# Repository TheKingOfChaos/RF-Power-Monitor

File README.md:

# RF-Power-Monitor

A mains power monitor built on a Raspberry Pi Pico with a W5500 Ethernet module. It reports whether mains power is present over SNMP v1 and v2c, including traps, together with standard interface statistics (IF-MIB), the CPU temperature and the ambient temperature (TMP1075 on the carrier board), so it can be monitored by LibreNMS or any other SNMP manager. It is configured through a menu on the USB serial port or a web page.

Current version: **3.6.1** (see [CHANGELOG.md](CHANGELOG.md)).

## Overview

An isolated detector (optocoupler with filtering) turns mains presence into a clean 3.3 V level on GPIO27; in the test setup an IKEA smart plug in front of it lets the tests switch mains off and on. The Pico's core 1 samples GPIO27 and the reset button (GPIO22) every millisecond; core 0 runs the network, the SNMP agent, the web page and the serial menu. Settings live in the Pico's flash in two copies, and the W5500 provides 10/100 Ethernet over SPI. On the network the device gets its address by DHCP (or a static IP), is reachable as `RF-Power-XXXXXX.local` (mDNS; XXXXXX = the last 6 hex digits of its MAC), answers SNMP v1/v2c on UDP 161, sends traps on UDP 162, serves a configuration web page with login on TCP 80, sets its clock by NTP and sends its events to a syslog server, when the network has them. The USB serial port carries the configuration menu and the hardware-in-the-loop tests. More diagrams are in [docs/diagrams/](docs/diagrams/README.md).

## Status

| Feature | State |
|---|---|
| Ethernet with DHCP (default) or static IP | Working |
| Serial menu for all settings | Working |
| Settings stored in flash, power-cut safe | Working |
| Factory reset button (GPIO22, 10 s hold, LED feedback) | Working, tested with the real button |
| Mains power monitoring on GPIO27 (core 1, debounced, 60 s alarm) | Working, verified with real mains (automated with a smart plug) |
| SNMP v1 and v2c agent (Get, GetNext, GetBulk) with rate limiting and access log | Working, tested with net-snmp |
| SNMP traps in v1 or v2c (coldStart, authenticationFailure, mains, firmware) | Working, mains traps verified with real mains |
| Standard MIBs: SNMPv2-MIB, IF-MIB (64-bit), IP-MIB, MIB-II counters, HOST-RESOURCES-MIB, ENTITY-MIB, LLDP-MIB | Working |
| CPU temperature (RP2040) and ambient temperature (TMP1075) | Working |
| Web page with login (status and settings; can be turned off) | Working |
| Hostname for SNMP sysName, DHCP and mDNS (`name.local`) | Working |
| IPv6 dual stack: SLAAC, static address, DHCPv6 | Working |
| LLDP: the switch lists the device; the device shows the switch and port | Working |
| SNMP trap destination from DHCP option 224 | Working, tested with Kea 2.2.0 |
| LibreNMS OS definition | Working, tested with LibreNMS 26.10.2 |
| Signed firmware updates with rollback (3.3.0) and the [update site](update-server/README.md) (3.4.0) | Working, HIL-tested end to end |
| Time from NTP and syslog (RFC 5424) (3.6.0) | Working, tested with LibreNMS's syslog receiver |

See [TODO.md](TODO.md) for the detailed plan.

## Quick start

**Hardware.** A WIZnet W5500-EVB-Pico-PoE (or a Pico with a W5500 module on SPI0) on the carrier board, which holds the isolated mains detector, the TMP1075 and the factory reset button. Power comes over PoE or USB. Boards, wiring and pins: [docs/HARDWARE.md](docs/HARDWARE.md).

**Build and flash** (VS Code with PlatformIO; on Windows the WinUSB driver once, see [docs/TESTING.md](docs/TESTING.md#usb-driver-for-flashing)):

```powershell
$pio = "$env:USERPROFILE\.platformio\penv\Scripts\pio.exe"
& $pio run -e pico               # build
& $pio run -e pico -t upload     # build and flash (close PuTTY first)
```

If upload fails, hold BOOTSEL while plugging in the Pico and copy `.pio\build\pico\firmware_full.uf2` to the `RPI-RP2` drive. **Never put the plain `firmware.uf2` on a BOOTSEL drive:** it has no boot program and the device will not start. Use `firmware_full.uf2` or a release's `-usb.uf2`. Field releases, signing and the bench tool: [docs/DEVELOPMENT.md](docs/DEVELOPMENT.md) and [docs/SETUP_MANUAL.md](docs/SETUP_MANUAL.md).

**First login.** Open the USB serial port at 115200 baud (PuTTY, which sets DTR) and press Enter: menu option 1 shows the device's address and its default web password (`Web login: user admin, default password "..."`). Then open `http://<address>/` or `http://RF-Power-XXXXXX.local/` and log in as `admin`. Next steps: the [setup manual](docs/SETUP_MANUAL.md) to install a device, the [user manual](docs/USER_MANUAL.md) for daily use.

## Documentation

| Document | Contents |
|---|---|
| [docs/SETUP_MANUAL.md](docs/SETUP_MANUAL.md) | **Installing a device**: safety, assembly, first configuration, LibreNMS, proving the alarm works, update site, time and syslog, bench setup of a new board, firmware signing key, checklist |
| [docs/USER_MANUAL.md](docs/USER_MANUAL.md) | **Daily use**: LEDs, label, web page (incl. security and paths for scripts), what to do on an alarm, changing settings, the serial menu (every option and status line), factory reset, firmware update, troubleshooting |
| [docs/REFERENCE.md](docs/REFERENCE.md) | **How the device behaves, in detail**: network, LLDP, time and syslog, hostname, IPv6, mains monitoring, watchdog, factory reset, settings storage |
| [docs/HARDWARE.md](docs/HARDWARE.md) | What the firmware runs on, carrier board, rev 2 board, pin configuration |
| [docs/DEVELOPMENT.md](docs/DEVELOPMENT.md) | Building and flashing, tests in short, project structure |
| [docs/TESTING.md](docs/TESTING.md) | Test layers, how to run them, automated mains tests with a smart plug, what each suite covers |
| [docs/MIB.md](docs/MIB.md) | Every SNMP object (SNMPv2-MIB, IF-MIB, IP/ICMP/TCP/UDP, HOST-RESOURCES-MIB, ENTITY-MIB, LLDP-MIB, RF-POWER-MONITOR-MIB), traps, v1/v2c differences, rate limiting, errors, limits |
| [docs/LIBRENMS.md](docs/LIBRENMS.md) | Monitoring the device with LibreNMS: install, sensors, alerts, traps, syslog, Docker test setup |
| [update-server/README.md](update-server/README.md) | The update site (Docker): device list, releases, assignments, shared key |
| [hardware/pico-poe-mains-carrier/](hardware/pico-poe-mains-carrier/README.md) | Carrier PCB rev 1.1 (KiCad 10): circuit, isolation, mounting, fab files for JLCPCB, 3D models |
| [hardware/rf-power-monitor-rev2/](hardware/rf-power-monitor-rev2/README.md) | Rev 2 board, RP2040 and W5500 on the board (ordered 2026-11-07, not built yet): differences from rev 1, pins, isolation, known limits, fab files |
| [docs/diagrams/](docs/diagrams/README.md) | Excalidraw diagrams (editable) of the system, firmware, SNMP, mains flow, settings, tests and the update site |
| [CHANGELOG.md](CHANGELOG.md) | What changed in each version |
| [SECURITY.md](SECURITY.md) | Supported versions, how to report a vulnerability privately, known limits by design |
| [.clinerules](.clinerules) | Project and test rules |

## Safety

- The mains detection circuit must be galvanically isolated (optocoupler). The carrier board's isolation (clearance, creepage, slot) is described in its [README](hardware/pico-poe-mains-carrier/README.md#isolation).
- Mains wiring must be done by a qualified person, in a closed enclosure, with the supply fused upstream.
- No GPIO may see more than 3.3 V.
- Ground all modules properly.

## License

MIT

The web page includes Bootstrap's CSS, Copyright 2011-2024 The Bootstrap Authors, MIT license (https://github.com/twbs/bootstrap/blob/main/LICENSE).

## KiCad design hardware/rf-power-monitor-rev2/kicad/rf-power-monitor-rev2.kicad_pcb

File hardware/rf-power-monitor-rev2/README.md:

# RF-Power-Monitor rev2

> **Status: ordered 2026-11-07, not built yet.** Every value below is a design limit, a calculation or a simulation. No rev2 board has been assembled or measured yet. The boards in use are still [rev 1.1](../pico-poe-mains-carrier/README.md).

Rev 1 is a carrier for the WIZnet W5500-EVB-Pico-PoE module. Rev 2 puts everything from that module on one board, except the PoE power stage, which stays the plug-in WIZnet WIZPoE-P1:

- RP2040 with 2 MB QSPI flash (W25Q16JV) and a 12 MHz crystal, copied from the Raspberry Pi Pico, so **the firmware runs unchanged** (Arduino-Pico board `pico`, same pin map)
- W5500 Ethernet controller, 25 MHz crystal, HanRun HR601680 magnetics and a shielded RJ45 with link/activity LEDs
- WIZPoE-P1 isolated IEEE 802.3af PD module (5 V), fed from the transformer centre taps (mode A) and the spare pairs (mode B), plugged into two 1x4 2.54 mm sockets or soldered
- TLV62569 1.5 MHz buck from VSYS (5 V) to 3.3 V; USB-C for the serial menu, flashing and bench power (VBUS to VSYS through a B5819W, as on the Pico)
- The rev 1 mains detector, TMP1075 and factory reset button, unchanged in function

100 x 64 mm, 2 layers, 1.6 mm, black solder mask, ENIG, assembled by JLCPCB (109 placed parts, 55 BOM lines, all with LCSC numbers). Designed with Adom AI Flow in KiCad 10 (brief: [design/brief.md](design/brief.md)). A full datasheet is in [design/datasheet/](design/datasheet/rf-power-monitor-rev2-datasheet.pdf).

| Top | Bottom |
|---|---|
|  |  |

## Rev 1 against rev 2

| | Rev 1.1 (carrier) | Rev 2 |
|---|---|---|
| MCU and Ethernet | On the W5500-EVB-Pico-PoE module | On the board (U4 RP2040, U3 W5500) |
| PoE | On the module | WIZPoE-P1 plug-in module (U2), fitted by hand |
| Size | 80 x 51.5 mm, plus the module | 100 x 64 mm, one board |
| Mains terminal | J1 | J4 |
| Mains ON / OFF LEDs | D1 green / D2 red | D3 green / D4 red |
| Factory reset button | SW1 | SW3 |
| BOOTSEL / RUN | On the module | SW1 / SW2 |
| Status LED (GP25) | On the module | D2, blue |
| SWD | On the module | J3, 1x3 2.54 mm, not fitted |
| Case | `hardware/Case` | Does not fit; a new case is still to be made |

## Firmware

The firmware is the same: the pins match [include/pins.h](../../include/pins.h).

| GPIO | Function | GPIO | Function |
|---|---|---|---|
| GP16 | W5500 MISO (SPI0) | GP4 / GP5 | I2C0 SDA / SCL, TMP1075 at 0x48 |
| GP17 | W5500 CS | GP22 | Factory reset (SW3 to GND, hold 10 s) |
| GP18 | W5500 SCK | GP24 | VBUS sense (as on the Pico) |
| GP19 | W5500 MOSI | GP25 | Status LED (D2) |
| GP20 | W5500 RST | GP27 | MAINS_OK, HIGH = mains present |
| GP21 | W5500 INT | | |

GP29 (ADC3) is not connected: the Pico's VSYS/3 divider was left out. The firmware does not read it. The datasheet's pin table still lists GP29 as VSYS/3; that entry is wrong.

The firmware reports `HARDWARE_REVISION` (entPhysicalHardwareRev) from [include/version.h](../../include/version.h), which still names rev 1.1. It needs a change when rev 2 boards are in use (TODO.md section 19).

Flash it like a Pico: hold BOOTSEL (SW1) while plugging in USB-C, or let `pio run -e pico -t upload` reset it into the bootloader.

## Connectors

Positions are in mm from the board's top-left corner.

| Ref | Connector | Position | Signals |
|---|---|---|---|
| J2 | RJ45 8P8C, shielded, LEDs (Kinghelm KH-RJ45-56-8P8C-D) | 7.9, 11.5, left edge | 10/100 Ethernet, PoE mode A and B. Its front sticks out 3.1 mm past the edge, to pass through the case wall |
| J1 | USB-C (HRO TYPE-C-31-M-12), USB 2.0 device | 95.6, 21.0, right edge | VBUS, D+, D-, CC1/CC2 5.1 k |
| J4 | 2-pole screw terminal, 5.08 mm, 250 VAC | 93.5, 52.0, right edge | 230 VAC L, N (mains sense only) |
| J3 | SWD, 1x3 2.54 mm, not fitted | 78.8, 10.0 | 1 SWCLK, 2 GND, 3 SWDIO (Pico order) |
| U2 | WIZPoE-P1 sockets, 2 x 1x4 2.54 mm | 21.5, 33.5 | VC1+/- (centre taps), VC2+/- (spare pairs), 5 V, GND |

Mounting: 4x M3 (3.2 mm) at (3.5, 60.5), (36.0, 60.5), (96.5, 3.5) and (96.5, 38.0). The tallest parts are J2, J4 and the WIZPoE-P1 on its sockets.

## Isolation

| Boundary | Clearance | Creepage | How |
|---|---|---|---|
| 230 VAC mains sense to everything else | 6.5 mm | 6.4 mm | Rev 1 rules, as DRC rules in `kicad/rf-power-monitor-rev2.kicad_dru`; 5 kVrms optocoupler (U6 LTV-814S); routed slot under U6; no copper pour in the mains area; silkscreen frame with a hazardous-voltage warning |
| Ethernet line side and PoE to logic | 2.0 mm | | 1500 Vrms (802.3, HR601680 hipot rating); Bob Smith termination to chassis |

The mains loop is fused (F1, T 1 A 250 VAC) and carries about 1.2 mA. Wiring to mains must be done by a qualified person, the board must sit in a closed enclosure, and the supply must be fused upstream. The mains section has not been hipot tested.

## Known limits

From the design checks (details in the datasheet, section 9):

- **WIZPoE-P1 minimum load:** the module specifies 150 mA minimum on 5 V; the board draws about 134 mA. Check that the module does not cycle at this load; if it does, add a bleed load.
- **HR601680 is not a PoE-rated transformer.** Its centre taps carry about 19 mA DC here (802.3af allows 350 mA per pair): low risk, but outside its rating.
- No TVS diodes on the Ethernet, USB or mains connectors; no EMC or safety testing.
- The RP2040's exposed pad has 3 thermal vias (AI Flow asks for 6); the thermal check passed at about 0.1 W.
- 19 small passives carry their reference on the fabrication layer only; 7 test points are unlabelled.

## Design checks

- ERC: 0 violations.
- DRC (KiCad 10, re-run 2026-11-03 on the saved board): 0 errors, 0 unconnected; 2 silkscreen warnings at U6.
- Schematic parity: 124 warnings, none of them a wrong connection. 85 are a schematic field ("Note") that the footprints do not carry. 39 are pins the schematic marks unconnected that have no net on the board (spare RP2040 GPIOs, W5500 reserved pins, NC pins).
- Calculations in `design/calcs.json` (`design/calcs.py`), buck simulation in `design/sim/` (ngspice, 4.7 mV ripple at 0.3 A).
- Bring-up measurements to take on the first board (rails, crystals, W5500 reset and SPI, mains sense, LEDs): `design/tests.json`.

## Files

| Path | Contents |
|---|---|
| `kicad/` | KiCad 10 project: `rf-power-monitor-rev2.kicad_pro`, `.kicad_sch`, `.kicad_pcb`, `.kicad_dru` |
| `kicad/lib/` | Project symbols and footprints (`RFPM_Rev2`) and the board's parts library (`pcm/`, copy of the AI Flow wiki package, with 3D models) |
| `kicad/tools/` | `gen_sch.py` (schematic from `design/netlist.json`), `gen_pcb.py` (placement and outline; routing is AI Flow's), `fab.sh` (fab files), helpers |
| `design/` | Brief, requirements, netlist, BOM with LCSC numbers and stock (2026-11-02), calculations, simulation, bring-up tests, schematic PDF, datasheet |
| `out/fab/` | Gerbers (zip), JLCPCB BOM and CPL, schematic PDF: see its [README](out/fab/README.md) for the order settings |
| `out/3d/` | 3D model as GLB, and the STEP zipped (`rf-power-monitor-rev2-step.zip`, the STEP itself is about 60 MB) |
| `out/img/` | Renders: top, bottom, isometric, schematic, layout and field-solve pictures |
| `aiflow/` | AI Flow spec and placement moves |

The schematic is generated: change `design/netlist.json` and run `python3 kicad/tools/gen_sch.py`, not the `.kicad_sch` by hand. The routed board is edited in KiCad. After any change to the board, save it and run `bash kicad/tools/fab.sh` from this folder (needs `kicad-cli` and `zip`, e.g. in WSL) to regenerate `out/fab/`.

AI Flow's working files (`aiflow-run/`, board iterations, field solves, logs) and the vendor datasheets stay out of git; see `.gitignore`.

## Ordering

Upload `out/fab/rf-power-monitor-rev2-gerbers.zip` to JLCPCB with 2 layers, 1.6 mm, 1 oz, black mask, white silkscreen, ENIG, and the BOM and CPL for assembly. U2 (WIZPoE-P1) and J3 (SWD) are not assembled: order the WIZPoE-P1 separately with two 1x4 2.54 mm female sockets. Check the rotation of J1 (USB-C) and J2 (RJ45) in JLCPCB's placement preview.

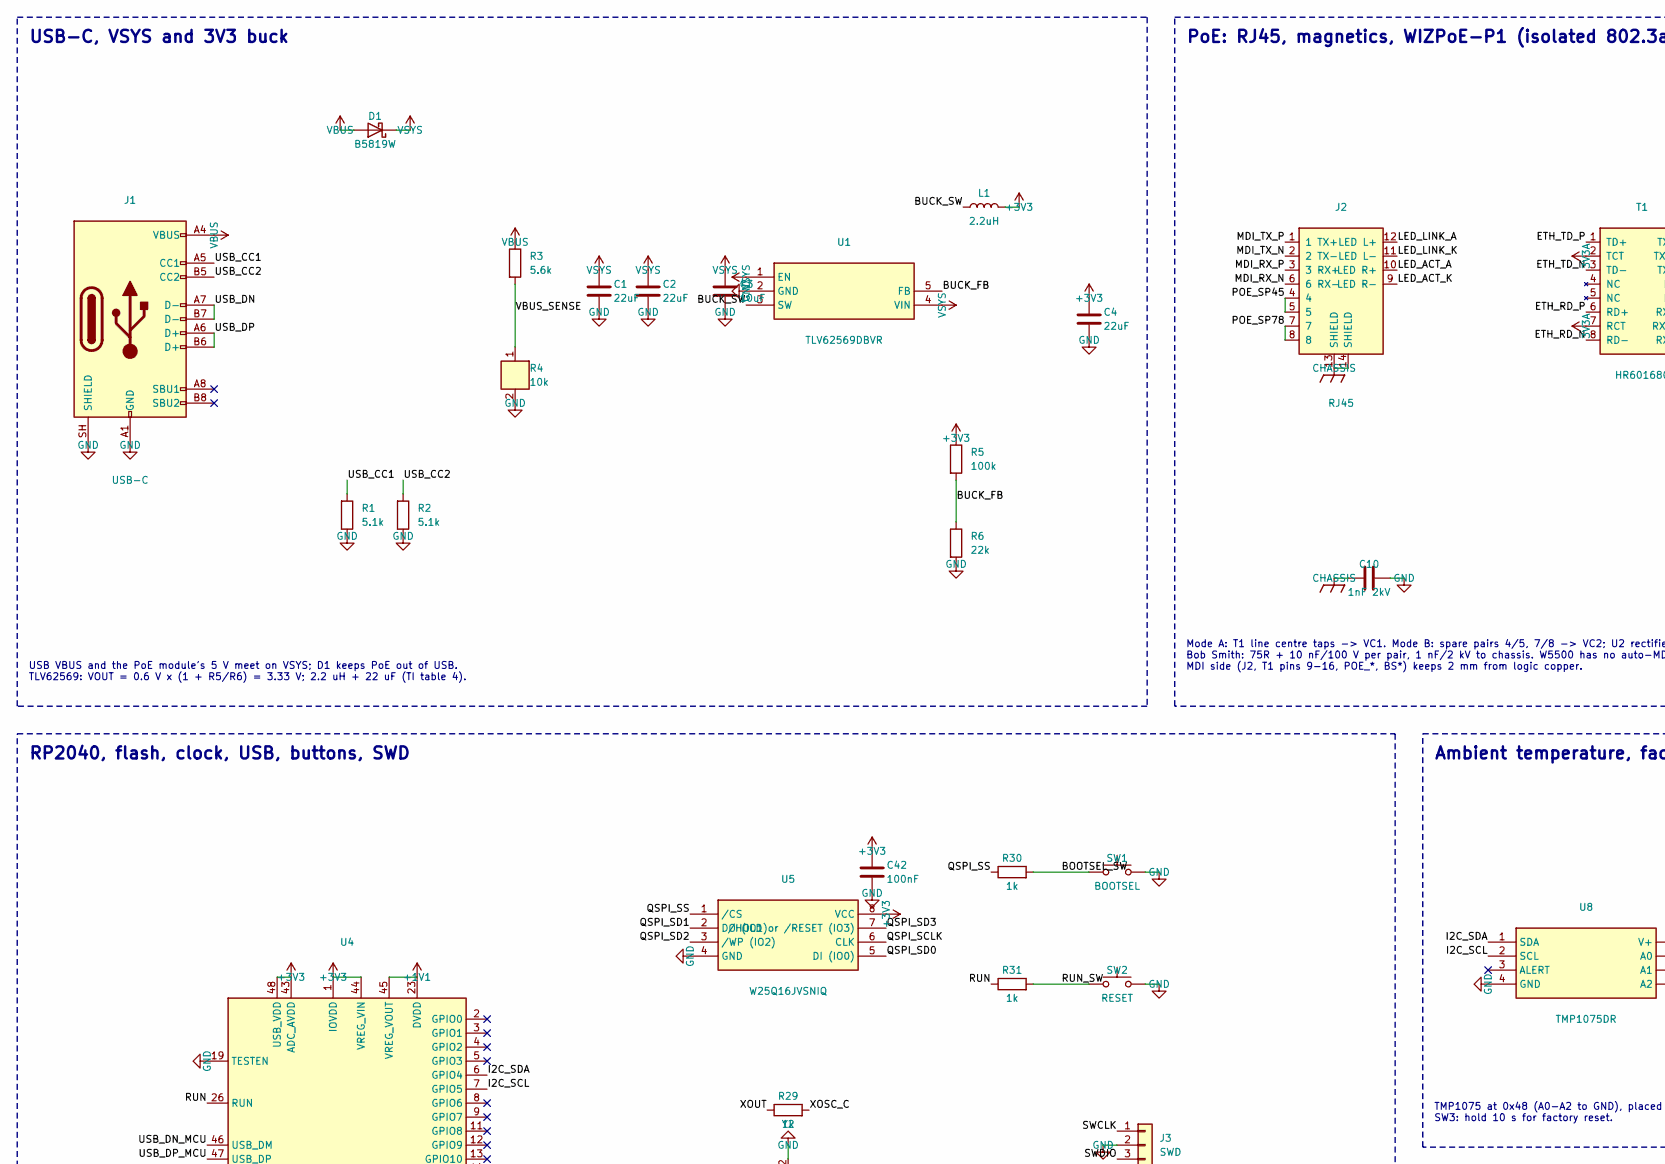
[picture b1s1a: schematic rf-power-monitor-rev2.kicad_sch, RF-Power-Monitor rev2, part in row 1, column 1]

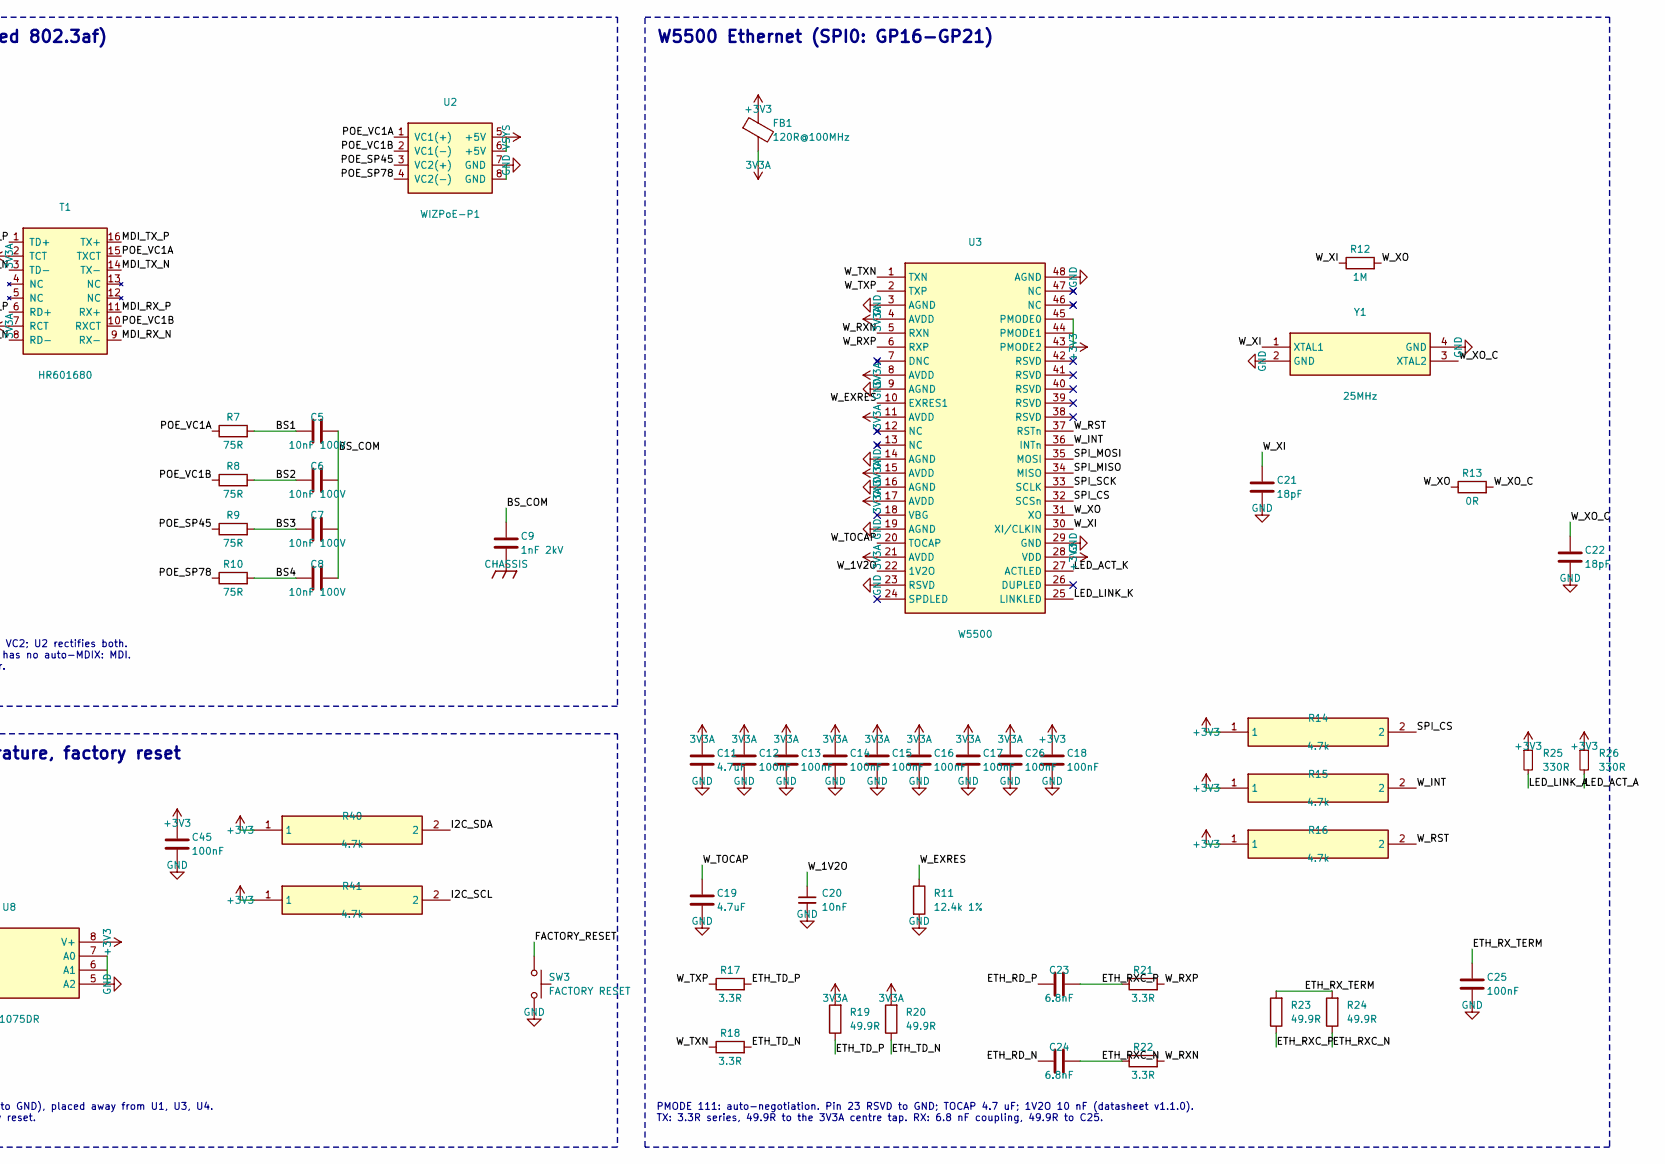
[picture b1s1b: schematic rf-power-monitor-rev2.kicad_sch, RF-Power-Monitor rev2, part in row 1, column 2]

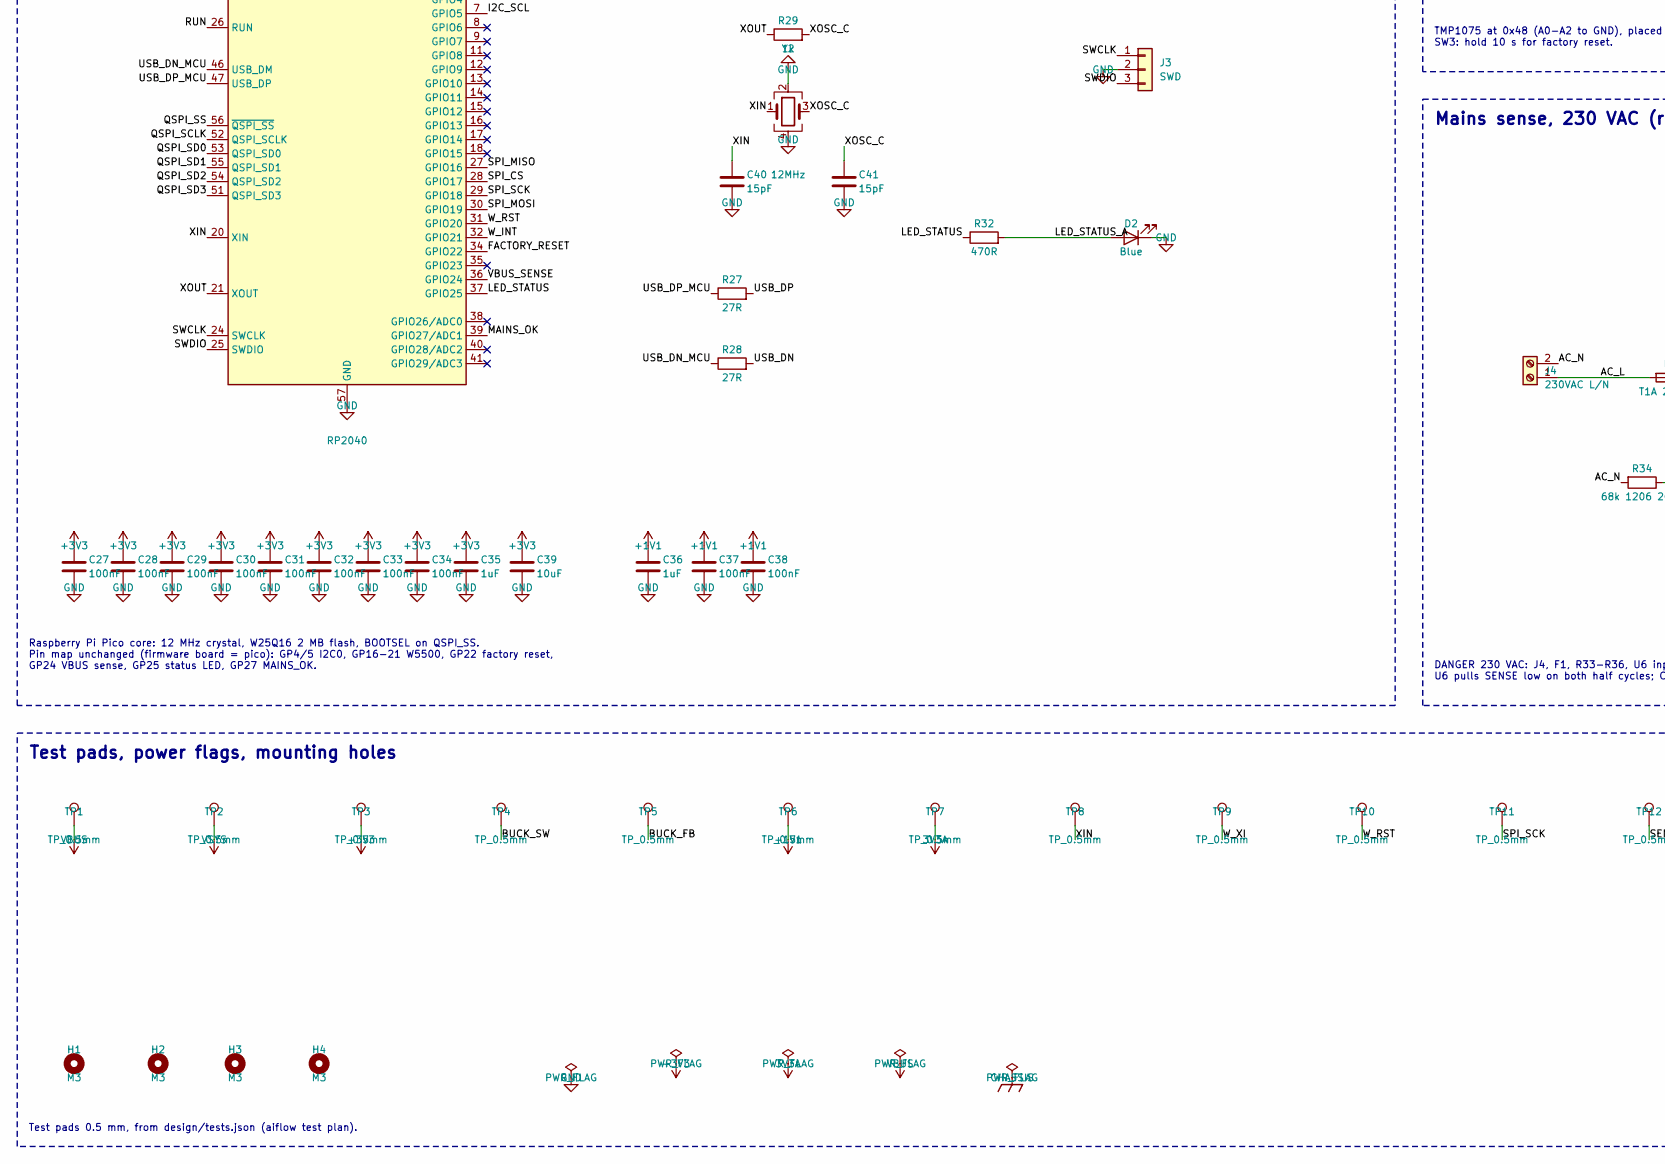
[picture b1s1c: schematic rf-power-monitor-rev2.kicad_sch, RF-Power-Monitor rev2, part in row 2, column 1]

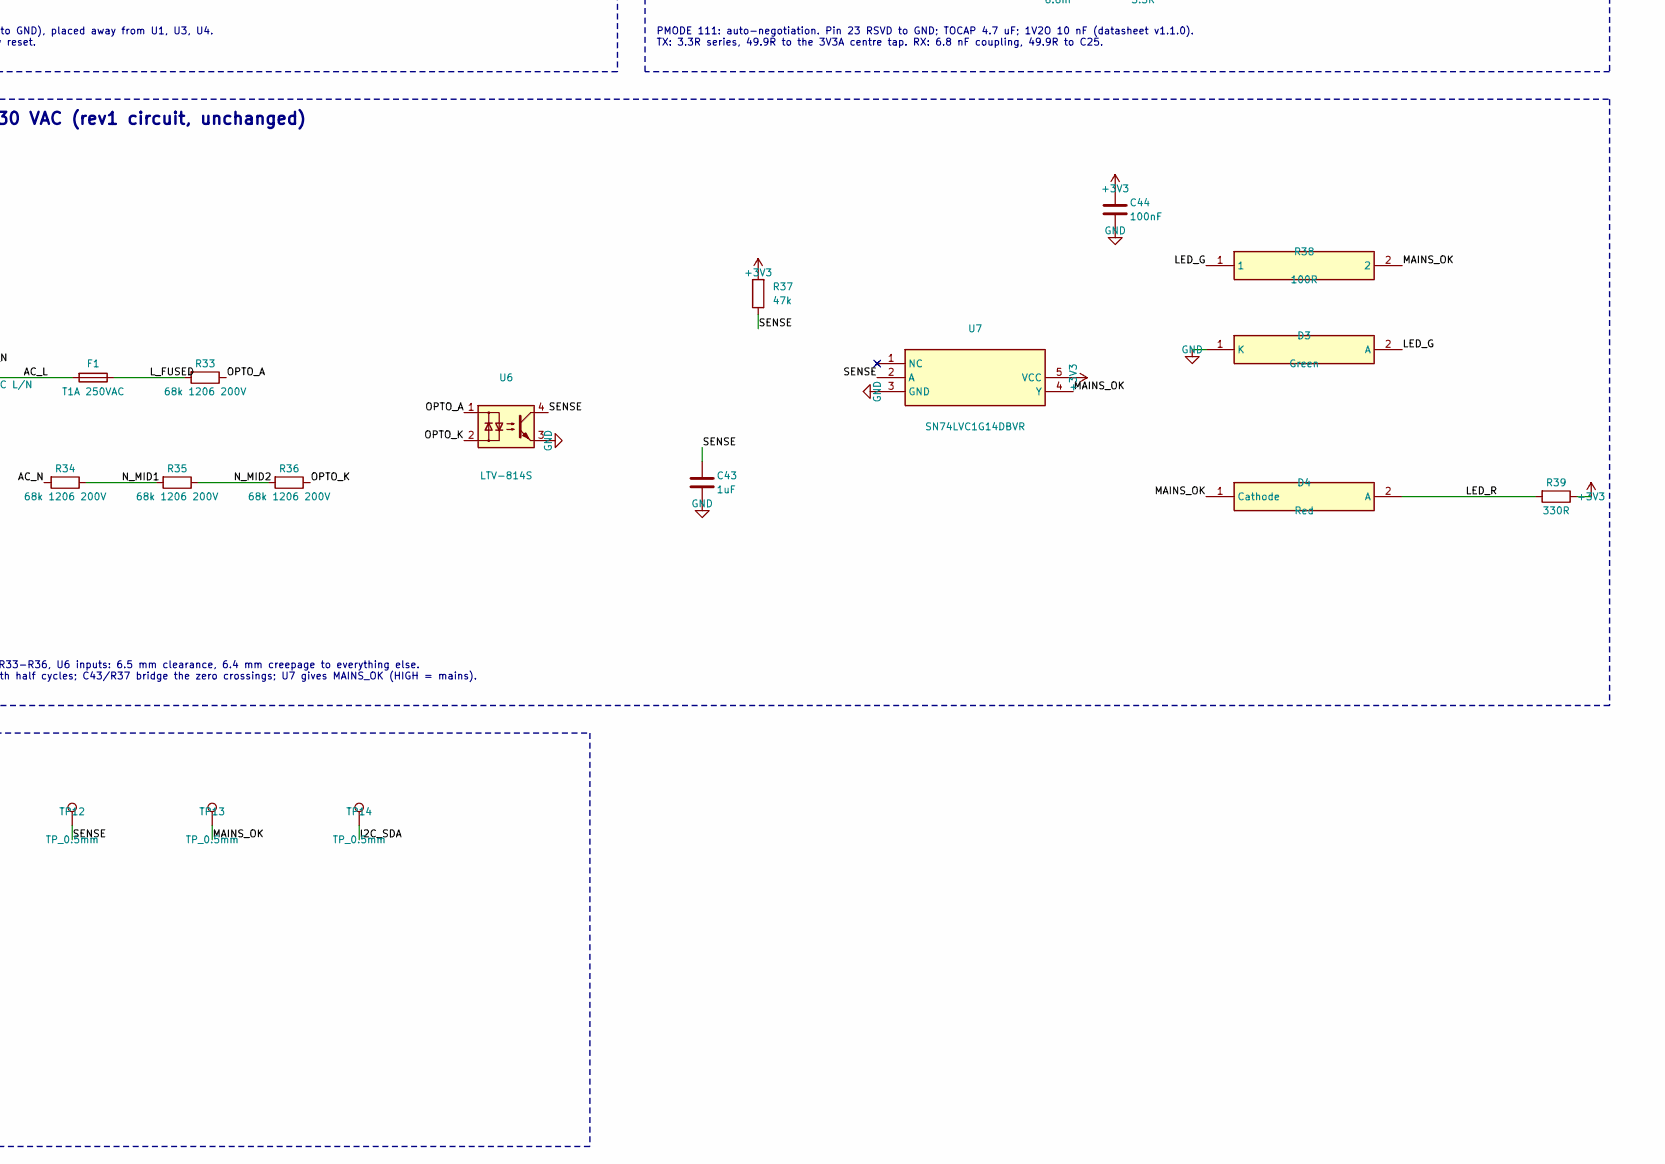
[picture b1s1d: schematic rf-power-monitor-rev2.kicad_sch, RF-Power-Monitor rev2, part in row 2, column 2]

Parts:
C1, C2, C4: 22uF; CL21A226MAQNNNE; MPN CL21A226MAQNNNE; LCSC C45783
C3, C39: 10uF; C_0805_2012Metric; MPN CL21A106KAYNNNE; LCSC C15850
C5, C6, C7, C8: 10nF 100V; C_0603_1608Metric; MPN CC0603KRX7R0BB103; LCSC C107059
C9, C10: 1nF 2kV; C_1808_4520Metric; MPN 1808B102K202NT; LCSC C81332
C11, C19: 4.7uF; CL10A475KO8NNNC; MPN CL10A475KO8NNNC; LCSC C19666
C12, C13, C14, C15, C16, C17, C18, C25, C26, C27, C28, C29, C30, C31, C32, C33, C34, C37, C38, C42, C44, C45: 100nF; C_0402_1005Metric; MPN CL05B104KO5NNNC; LCSC C1525
C20: 10nF; CL05B103KB5NNNC; MPN CL05B103KB5NNNC; LCSC C15195
C21, C22: 18pF; C_0402_1005Metric_0402CG180J500NT; MPN 0402CG180J500NT; LCSC C1549
C23, C24: 6.8nF; C_0402_1005Metric; MPN 0402B682K500NT; LCSC C1542
C35, C36: 1uF; C_0402_1005Metric_CL05A105KA5NQNC; MPN CL05A105KA5NQNC; LCSC C52923
C40, C41: 15pF; C_0402_1005Metric_0402CG150J500NT; MPN 0402CG150J500NT; LCSC C1548
C43: 1uF; C_0603_1608Metric; MPN CL10B105KB8NQNC; LCSC C5199872
D1: B5819W; D_SOD-123; MPN B5819W SL; LCSC C8598
D2: Blue; LED_0603_1608Metric; MPN 19-217/BHC-ZL1M2RY/6T; LCSC C2986058
D3: Green; LED_0805_2012Metric; MPN KT-0805G; LCSC C2297
D4: Red; LED_0805_2012Metric; MPN NCD0805R1; LCSC C84256
F1: T1A 250VAC; Fuse_Schurter_UMT250; MPN SCT1032T1A250V; LCSC C19712559
FB1: 120R@100MHz; L_0603_1608Metric; MPN GZ1608D121TF; LCSC C12391
H1, H2, H3, H4: M3; MountingHole_3.2mm_M3
J1: USB-C; USB_C_Receptacle_HRO_TYPE-C-31-M-12; MPN TYPE-C-31-M-12; LCSC C165948
J2: RJ45; RJ45-TH_KH-RJ45-56-8P8C-D; MPN KH-RJ45-56-8P8C-D; LCSC C2828082
J3: SWD; PinHeader_1x03_P2.54mm_Vertical
J4: 230VAC L/N; TerminalBlock_Phoenix_MKDS-1,5-2-5.08_1x02_P5.08mm_Horizont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; MPN WJ500V-5.08-2P; LCSC C8465
L1: 2.2uH; IND-SMD_L3.0-W3.0; MPN SWPA3015S2R2MT; LCSC C43389
R1, R2: 5.1k; R_0402_1005Metric; MPN 0402WGF5101TCE; LCSC C25905
R3: 5.6k; R_0402_1005Metric; MPN 0402WGF5601TCE; LCSC C25908
R4: 10k; R_0402_1005Metric_RC0402FR-0710KL; MPN RC0402FR-0710KL; LCSC C60490
R5: 100k; R_0402_1005Metric_0402WGF1003TCE; MPN 0402WGF1003TCE; LCSC C25741
R6: 22k; R_0402_1005Metric; MPN RC0402FR-0722KL; LCSC C82868
R7, R8, R9, R10: 75R; R_0402_1005Metric; MPN RC0402FR-0775RL; LCSC C114757
R11: 12.4k 1%; R_0402_1005Metric; MPN 0402WGF1242TCE; LCSC C11692
R12: 1M; R_0402_1005Metric; MPN 0402WGF1004TCE; LCSC C26083
R13: 0R; R_0402_1005Metric_0402WGF1003TCE; MPN 0402WGF0000TCE; LCSC C17168
R14, R15, R16, R40, R41: 4.7k; R_0402_1005Metric_0402WGF1003TCE; MPN 0402WGF4701TCE; LCSC C25900
R17, R18, R21, R22: 3.3R; R_0402_1005Metric; MPN RC0402FR-073R3L; LCSC C137986
R19, R20, R23, R24: 49.9R; R_0402_1005Metric; MPN 0402WGF499JTCE; LCSC C25120
R25, R26: 330R; 0402WGF3300TCE; MPN 0402WGF3300TCE; LCSC C25104
R27, R28: 27R; R_0402_1005Metric; MPN RC0402FR-0727RL; LCSC C138021
R29, R30, R31: 1k; R_0402_1005Metric_0402WGF1003TCE; MPN 0402WGF1001TCE; LCSC C11702
R32: 470R; R_0402_1005Metric; MPN RC0402FR-07470RL; LCSC C114877
R33, R34, R35, R36: 68k 1206 200V; R_1206_3216Metric; MPN 1206W4F6802T5E; LCSC C25834
R37: 47k; R_0603_1608Metric; MPN 0603WAF4702T5E; LCSC C25819
R38: 100R; R_0603_1608Metric; MPN 0603WAF1000T5E; LCSC C22775
R39: 330R; R_0603_1608Metric; MPN RC0603FR-07330RL; LCSC C105881
SW1: BOOTSEL; SW_Push_1P1T_XKB_TS-1187A; MPN TS-1187A-B-A-B; LCSC C318884
SW2: RESET; SW_Push_1P1T_XKB_TS-1187A; MPN TS-1187A-B-A-B; LCSC C318884
SW3: FACTORY RESET; SW_Push_1P1T_XKB_TS-1187A; MPN TS-1187A-B-A-B; LCSC C318884
T1: HR601680; SMD-16_L12.7-W7.2-P1.27-LS9.5-BL; MPN HR601680; LCSC C242560
TP1, TP2, TP3, TP4, TP5, TP6, TP7, TP8, TP9, TP10, TP11, TP12, TP13, TP14: TP_0.5mm; TestPoint_Pad_D0.5mm; MPN Adom_TestPoint_D0.5mm
U1: TLV62569DBVR; SOT-23-5; MPN TLV62569DBVR; LCSC C141836
U2: WIZPoE-P1; MPN WIZPoE-P1
U3: W5500; LQFP-48_7x7mm_P0.5mm; MPN W5500; LCSC C32843
U4: RP2040; QFN-56-1EP_7x7mm_P0.4mm_EP3.2x3.2mm; MPN RP2040; LCSC C2040
U5: W25Q16JVSNIQ; SOIC-8_3.9x4.9mm_P1.27mm; MPN W25Q16JVSNIQ; LCSC C2456211
U6: LTV-814S; SMDIP-4_W9.53mm; MPN LTV-814S-TA1; LCSC C125118
U7: SN74LVC1G14DBVR; SOT-23-5; MPN SN74LVC1G14DBVR; LCSC C7835
U8: TMP1075DR; SOIC-8_3.9x4.9mm_P1.27mm; MPN TMP1075DR; LCSC C2878381
Y1: 25MHz; Crystal_SMD_3225-4Pin_3.2x2.5mm; MPN X322525MOB4SI; LCSC C9006
Y2: 12MHz; Crystal_SMD_Abracon_ABM8AIG-4Pin_3.2x2.5mm; MPN ABM8-272-T3; LCSC C20625731

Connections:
3V3A: C11.1, C12.1, C13.1, C14.1, C15.1, C16.1, C17.1, C26.1, FB1.2, R19.2, R20.2, T1.2 (TCT), T1.7 (RCT), TP7.1, U3.4 (AVDD), U3.8 (AVDD), U3.11 (AVDD), U3.15 (AVDD), U3.17 (AVDD), U3.21 (AVDD)
+1V1: C36.1, C37.1, C38.1, TP6.1, U4.23 (DVDD), U4.45 (VREG_VOUT), U4.50 (DVDD)
+3V3: C4.1, C18.1, C27.1, C28.1, C29.1, C30.1, C31.1, C32.1, C33.1, C34.1, C35.1, C39.1, C42.1, C44.1, C45.1, FB1.1, L1.2, R5.1, R14.1, R15.1, R16.1, R25.1, R26.1, R37.2, R39.1, R40.1, R41.1, TP3.1, U3.28 (VDD), U3.43 (PMODE2), U3.44 (PMODE1), U3.45 (PMODE0), U4.1 (IOVDD), U4.10 (IOVDD), U4.22 (IOVDD), U4.33 (IOVDD), U4.42 (IOVDD), U4.43 (ADC_AVDD), U4.44 (VREG_VIN), U4.48 (USB_VDD), U4.49 (IOVDD), U5.8 (VCC), U7.5 (VCC), U8.8 (V+)
/AC_L: F1.2, J4.1
/AC_N: J4.2, R34.2
/BOOTSEL_SW: R30.2, SW1.1
/BS1: C5.1, R7.2
/BS2: C6.1, R8.2
/BS3: C7.1, R9.2
/BS4: C8.1, R10.2
/BS_COM: C5.2, C6.2, C7.2, C8.2, C9.1
/BUCK_FB: R5.2, R6.1, TP5.1, U1.5 (FB)
/BUCK_SW: L1.1, TP4.1, U1.3 (SW)
/ETH_RD_N: C24.1, T1.8 (RD-)
/ETH_RD_P: C23.1, T1.6 (RD+)
/ETH_RXC_N: C24.2, R22.1, R24.1
/ETH_RXC_P: C23.2, R21.1, R23.1
/ETH_RX_TERM: C25.1, R23.2, R24.2
/ETH_TD_N: R18.2, R20.1, T1.3 (TD-)
/ETH_TD_P: R17.2, R19.1, T1.1 (TD+)
/FACTORY_RESET: SW3.1, U4.34 (GPIO22)
/I2C_SCL: R41.2, U4.7 (GPIO5), U8.2 (SCL)
/I2C_SDA: R40.2, TP14.1, U4.6 (GPIO4), U8.1 (SDA)
/LED_ACT_A: J2.10 (LED R+), R26.2
/LED_ACT_K: J2.9 (LED R-), U3.27 (ACTLED)
/LED_G: D3.2 (A), R38.1
/LED_LINK_A: J2.12 (LED L+), R25.2
/LED_LINK_K: J2.11 (LED L-), U3.25 (LINKLED)
/LED_R: D4.2 (A), R39.2
/LED_STATUS: R32.1, U4.37 (GPIO25)
/LED_STATUS_A: D2.2 (A), R32.2
/L_FUSED: F1.1, R33.2
/MAINS_OK: D4.1 (Cathode), R38.2, TP13.1, U4.39 (GPIO27/ADC1), U7.4 (Y)
/MDI_RX_N: J2.6 (6 RX-), T1.9 (RX-)
/MDI_RX_P: J2.3 (3 RX+), T1.11 (RX+)
/MDI_TX_N: J2.2 (2 TX-), T1.14 (TX-)
/MDI_TX_P: J2.1 (1 TX+), T1.16 (TX+)
/N_MID1: R34.1, R35.2
/N_MID2: R35.1, R36.2
/OPTO_A: R33.1, U6.1
/OPTO_K: R36.1, U6.2
/POE_SP45: J2.4, J2.5, R9.1, U2.3 (VC2(+))
/POE_SP78: J2.7, J2.8, R10.1, U2.4 (VC2(-))
/POE_VC1A: R7.1, T1.15 (TXCT), U2.1 (VC1(+))
/POE_VC1B: R8.1, T1.10 (RXCT), U2.2 (VC1(-))
/QSPI_SCLK: U4.52 (QSPI_SCLK), U5.6 (CLK)
/QSPI_SD0: U4.53 (QSPI_SD0), U5.5 (DI (IO0))
/QSPI_SD1: U4.55 (QSPI_SD1), U5.2 (DO (IO1))
/QSPI_SD2: U4.54 (QSPI_SD2), U5.3 (/WP (IO2))
/QSPI_SD3: U4.51 (QSPI_SD3), U5.7 (/HOLD or /RESET (IO3))
/QSPI_SS: R30.1, U4.56 (~QSPI_SS), U5.1 (/CS)
/RUN: R31.1, U4.26 (RUN)
/RUN_SW: R31.2, SW2.1
/SENSE: C43.1, R37.1, TP12.1, U6.4, U7.2 (A)
/SPI_CS: R14.2, U3.32 (SCSn), U4.28 (GPIO17)
/SPI_MISO: U3.34 (MISO), U4.27 (GPIO16)
/SPI_MOSI: U3.35 (MOSI), U4.30 (GPIO19)
/SPI_SCK: TP11.1, U3.33 (SCLK), U4.29 (GPIO18)
/SWCLK: J3.1, U4.24 (SWCLK)
/SWDIO: J3.3, U4.25 (SWDIO)
/USB_CC1: J1.A5 (CC1), R1.1
/USB_CC2: J1.B5 (CC2), R2.1
/USB_DN: J1.A7 (D-), J1.B7 (D-), R28.2
/USB_DN_MCU: R28.1, U4.46 (USB_DM)
/USB_DP: J1.A6 (D+), J1.B6 (D+), R27.2
/USB_DP_MCU: R27.1, U4.47 (USB_DP)
/VBUS_SENSE: R3.2, R4.1, U4.36 (GPIO24)
/W_1V2O: C20.1, U3.22 (1V2O)
/W_EXRES: R11.1, U3.10 (EXRES1)
/W_INT: R15.2, U3.36 (INTn), U4.32 (GPIO21)
/W_RST: R16.2, TP10.1, U3.37 (RSTn), U4.31 (GPIO20)
/W_RXN: R22.2, U3.5 (RXN)
/W_RXP: R21.2, U3.6 (RXP)
/W_TOCAP: C19.1, U3.20 (TOCAP)
/W_TXN: R18.1, U3.1 (TXN)
/W_TXP: R17.1, U3.2 (TXP)
/W_XI: C21.1, R12.1, TP9.1, U3.30 (XI/CLKIN), Y1.1 (XTAL1)
/W_XO: R12.2, R13.1, U3.31 (XO)
/W_XO_C: C22.1, R13.2, Y1.3 (XTAL2)
/XIN: C40.1, TP8.1, U4.20 (XIN), Y2.1
/XOSC_C: C41.1, R29.2, Y2.3
/XOUT: R29.1, U4.21 (XOUT)
CHASSIS: C9.2, C10.1, J2.13 (SHIELD), J2.14 (SHIELD)
GND: C1.2, C2.2, C3.2, C4.2, C10.2, C11.2, C12.2, C13.2, C14.2, C15.2, C16.2, C17.2, C18.2, C19.2, C20.2, C21.2, C22.2, C25.2, C26.2, C27.2, C28.2, C29.2, C30.2, C31.2, C32.2, C33.2, C34.2, C35.2, C36.2, C37.2, C38.2, C39.2, C40.2, C41.2, C42.2, C43.2, C44.2, C45.2, D2.1 (K), D3.1 (K), J1.A1 (GND), J1.A12 (GND), J1.B1 (GND), J1.B12 (GND), J1.SH (SHIELD), J3.2, R1.2, R2.2, R4.2, R6.2, R11.2, SW1.2, SW2.2, SW3.2, U1.2 (GND), U2.7 (GND), U2.8 (GND), U3.3 (AGND), U3.9 (AGND), U3.14 (AGND), U3.16 (AGND), U3.19 (AGND), U3.23 (RSVD), U3.29 (GND), U3.48 (AGND), U4.19 (TESTEN), U4.57 (GND), U5.4 (GND), U6.3, U7.3 (GND), U8.4 (GND), U8.5 (A2), U8.6 (A1), U8.7 (A0), Y1.2 (GND), Y1.4 (GND), Y2.2, Y2.4
VBUS: D1.2 (A), J1.A4 (VBUS), J1.A9 (VBUS), J1.B4 (VBUS), J1.B9 (VBUS), R3.1, TP1.1
VSYS: C1.1, C2.1, C3.1, D1.1 (K), TP2.1, U1.1 (EN), U1.4 (VIN), U2.5 (+5V), U2.6 (+5V)

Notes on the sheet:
USB-C, VSYS and 3V3 buck
USB VBUS and the PoE module's 5 V meet on VSYS; D1 keeps PoE out of USB. TLV62569: VOUT = 0.6 V x (1 + R5/R6) = 3.33 V; 2.2 uH + 22 uF (TI table 4).
PoE: RJ45, magnetics, WIZPoE-P1 (isolated 802.3af)
Mode A: T1 line centre taps -> VC1. Mode B: spare pairs 4/5, 7/8 -> VC2; U2 rectifies both. Bob Smith: 75R + 10 nF/100 V per pair, 1 nF/2 kV to chassis. W5500 has no auto-MDIX: MDI. MDI side (J2, T1 pins 9-16, POE_*, BS*) keeps 2 mm from logic copper.
W5500 Ethernet (SPI0: GP16-GP21)
PMODE 111: auto-negotiation. Pin 23 RSVD to GND; TOCAP 4.7 uF; 1V2O 10 nF (datasheet v1.1.0). TX: 3.3R series, 49.9R to the 3V3A centre tap. RX: 6.8 nF coupling, 49.9R to C25.
RP2040, flash, clock, USB, buttons, SWD
Raspberry Pi Pico core: 12 MHz crystal, W25Q16 2 MB flash, BOOTSEL on QSPI_SS. Pin map unchanged (firmware board = pico): GP4/5 I2C0, GP16-21 W5500, GP22 factory reset, GP24 VBUS sense, GP25 status LED, GP27 MAINS_OK.
Ambient temperature, factory reset
TMP1075 at 0x48 (A0-A2 to GND), placed away from U1, U3, U4. SW3: hold 10 s for factory reset.
Mains sense, 230 VAC (rev1 circuit, unchanged)
DANGER 230 VAC: J4, F1, R33-R36, U6 inputs: 6.5 mm clearance, 6.4 mm creepage to everything else. U6 pulls SENSE low on both half cycles; C43/R37 bridge the zero crossings; U7 gives MAINS_OK (HIGH = mains).
Test pads, power flags, mounting holes
Test pads 0.5 mm, from design/tests.json (aiflow test plan).
